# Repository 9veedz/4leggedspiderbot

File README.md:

# ESP32 Quadruped Spider Robot

> Built largely through vibe coding, iterating with an AI assistant rather than writing every line from scratch. Logic has been tested where possible, but review the code yourself before trusting it on real hardware, especially the servo angle limits.

A 4-legged (12-servo) walking robot controlled by an ESP32, with a built-in WiFi access point and web-based control interface for live tuning, calibration, and gait control — no app required, just a browser.

>  **This project is sponsored by [PCBWay](https://www.pcbway.com)!**

Many thanks to PCBWay for sponsoring this project with high-quality PCBs. As a small hobby project with no real following or funding, being approached by PCBWay for sponsorship genuinely means a lot. I'm truly grateful for the support — it's what made getting real boards in my hands possible. More details in the [sponsor section](#sponsor--pcbway) below.

> ⚠️ This is an ongoing hobby project — still actively being developed and subject to changes.
## Demo

**Walking gait**

**Body roll & pitch control**

> The robot moves significantly more fluidly than the videos suggest — the choppy appearance is purely down to the low frame rate of the recording. The inverse kinematics system interpolates each leg smoothly in real time; what you're seeing is a capture artifact, not the actual motion quality.

## Features

- **Inverse kinematics leg control** — each leg independently computes coxa/femur/tibia servo angles from X/Y/Z target positions.
- **Live web UI** — connects directly to the ESP32's own WiFi access point and serves a mobile-friendly control panel over WebSocket (`/ws`) with a captive portal so it opens automatically on connect.
- **Body posture control** — adjustable body height, width, stride length, pitch, and roll, with automatic tilt trim calculation per leg.
- **Walking gaits** — forward and reverse walking gaits using a diagonal-pair stepping pattern (lift → stride → push → recover).
- **Per-leg calibration** — manual servo angle control, configurable min/max safety limits, and offset trims per joint (coxa/femur/tibia), saved persistently to flash (ESP32 NVS/Preferences).
- **Per-leg power control** — individually or globally power legs on/off (releases servo PWM signal) for safe handling or storage.
- **Robot state machine** — `SIT`, `STAND`, `FORWARD`, `REVERSE` states drive automatic transitions between resting and walking behavior.

## Hardware

- ESP32 development board
- PCA9685 16-channel PWM/servo driver (I2C)
- 12x servos (3 per leg: coxa, femur, tibia)
- 4-leg chassis, with legs 1 and 2 mirrored relative to legs 0 and 3
- 3D-printed body: [Thingiverse Thing #2204279](https://www.thingiverse.com/thing:2204279), based on the design from [Instructables: DIY Spider Robot / Quad Robot / Quadruped](https://www.instructables.com/DIY-Spider-RobotQuad-robot-Quadruped/)

> **Important — before assembling the legs onto the 3D-printed body:** power each servo individually and set it to **90 degrees** *before* mounting the horn and locking the leg segments onto the printed body. The codebase has calls toward a `spiderCalibrate()` / `calibrateServos()` path, but it is not a complete, working calibration setup as-is — don't rely on it out of the box. Manually centering each servo to 90° before assembly (e.g. with a basic standalone test sketch) is the safer approach until calibration is properly wired up. The IK math and default offsets (`offC`/`offF`/`offT` = 90) assume each joint's mechanical zero/center point lines up with 90° on the servo. If a horn is attached and the leg geometry locked in at the wrong angle, the leg will be physically offset from where the code thinks it is, and you'll fight it with calibration offsets indefinitely instead of starting from a clean baseline.

| Leg | Coxa Pin | Femur Pin | Tibia Pin | Position    | Mirrored |
| --- | -------- | --------- | --------- | ----------- | -------- |
| 0   | 0        | 1         | 2         | Front-left  | No       |
| 1   | 3        | 4         | 5         | Front-right | Yes      |
| 2   | 6        | 7         | 8         | Back-left   | Yes      |
| 3   | 9        | 10        | 11        | Back-right  | No       |

### Leg Segment Lengths

Each leg has three segments, defined as constants in `SpiderLeg.cpp` and used directly in the inverse kinematics calculations:

| Segment | Joint | Length (mm) | Description                                |
| ------- | ----- | ----------- | ------------------------------------------ |
| L1      | Coxa  | 27.5        | Hip joint offset, rotates leg in X/Y plane |
| L2      | Femur | 55.0        | Upper leg segment                          |
| L3      | Tibia | 77.5        | Lower leg segment, reaches the ground      |

These are physical measurements of the chassis/leg hardware, used by `calculateIK()` to solve for coxa, femur, and tibia joint angles from a target X/Y/Z foot position. If you build this on different hardware, these three constants are the first thing to update to match your own leg dimensions.

## Project Structure

This is an Arduino IDE sketch. Arduino IDE requires a `.ino` file matching the sketch folder name, but all real logic lives in standard `.cpp`/`.h` files, which the IDE compiles automatically alongside it.

```
code/
├── SpiderRobot.ino     # Entry point: setup() / loop()
├── Spider.h / .cpp     # High-level robot behavior: stand, sit, walk, calibrate
├── SpiderLeg.h / .cpp  # Per-leg inverse kinematics & servo output
├── Robotstate.h / .cpp # Shared global state, persistence (flash/NVS)
├── Spiderserver.h / .cpp # WiFi AP, captive portal, WebSocket server
└── Webpage.h           # Embedded HTML/CSS/JS control panel (served from flash)
```

## Code Structure Notes

Each leg is its own object with its own pins and position, and handles its own mirroring internally. `Spider` just tells legs where to go. Makes gait code easier to read, and adding more legs later is mostly just adding more leg objects.

## Getting Started

1. Open `SpiderRobot.ino` in Arduino IDE.
2. Install required libraries via Library Manager:
  - `Adafruit PWM Servo Driver Library`
  - `ESPAsyncWebServer`
  - `AsyncTCP`
  - `ArduinoJson`
  - `DNSServer` (bundled with ESP32 core)
3. Select your ESP32 board under **Tools > Board**.
4. Wire the PCA9685 to the ESP32 via I2C and connect all 12 servos.
5. Flash the sketch.
6. On boot, the ESP32 creates a WiFi access point:
  - **SSID:** `ESP32_Spider`
  - **Password:** `12345678`
7. Connect to that network from a phone or laptop. A captive portal should prompt you to open the control page automatically (or browse to `192.168.4.1` manually).

> **Note:** The AP credentials are currently hardcoded in `Spiderserver.cpp`. Change them before deploying anywhere you don't fully control.

## Using the Web Interface

- **Robot Motion State** — switch between Sit / Stand / Forward / Reverse.
- **Body / Global** — tune body height, width, stride, pitch, and roll in real time.
- **Leg Select & Power** — choose which leg's parameters you're editing, and power individual or all legs on/off.
- **Geometry** — per-leg W/H/L trim offsets.
- **Servo Offsets** — per-joint calibration offsets (coxa/femur/tibia).
- **Servo Angle Control** — manually drive a joint to a specific angle (calibration mode).
- **Servo Min/Max** — set safe angle limits per joint to protect hardware.
- **Save to Flash** — persists all current settings to the ESP32's non-volatile storage.
- **Reload/Reset Defaults** — restores factory default values.

All changes apply live over WebSocket; no page reloads are needed.

## Understanding the Inverse Kinematics

If you want to understand how the leg IK math works before diving into `SpiderLeg.cpp`, this video explains it well:

📺 [Inverse Kinematics for a 3-segment leg — YouTube](https://youtu.be/HjmIOKSp7v4?si=qGuz0ecaw_1wg7XF)

## How to Swap in Your Own Control Scheme

The main robot logic lives in `SpiderLeg`, `Spider`, and `Robotstate` — those are the brains. `Spiderserver` and `Webpage` are just how *this* project talks to the robot over WiFi/WebSocket. You can rip those out entirely and replace them with whatever you want — a Bluetooth remote, an RC receiver, a gamepad, a serial interface — as long as you write to the same variables in `Robotstate`.

Everything the robot responds to is exposed as simple global variables you can read or write from anywhere:

**Body / Posture**

| Variable     | Type    | Description                       |
| ------------ | ------- | --------------------------------- |
| `bodyHeight` | `float` | Overall body height offset        |
| `bodyWidth`  | `float` | Overall body width offset         |
| `bodyStride` | `float` | Step length used in walking gaits |
| `bodyPitch`  | `float` | Forward/back tilt of the body     |
| `bodyRoll`   | `float` | Left/right tilt of the body       |

**Robot State**

| Variable         | Type             | Description                                                                                                                                            |
| ---------------- | ---------------- | ------------------------------------------------------------------------------------------------------------------------------------------------------ |
| `commandedState` | `RobotStateMode` | What you want the robot to do: `SIT`, `STAND`, `FORWARD`, `REVERSE`                                                                                    |
| `currentState`   | `RobotStateMode` | What the robot is currently doing — declared but not yet actively updated separately from `commandedState`, reserved for future state transition logic |
| `activeLeg`      | `int`            | Which leg (0–3) is selected for tuning                                                                                                                 |
| `calibrateMode`  | `bool`           | ⚠️ Declared but currently unused — reserved for a future calibration mode flow                                                                         |
| `calibrateLeg`   | `int`            | ⚠️ Declared but currently unused — intended to track which leg is being calibrated independently of `activeLeg`                                        |

**Computed Per-Leg Arrays** (auto-updated by `updateKinematicArrays()`)

| Variable        | Type    | Description                                         |
| --------------- | ------- | --------------------------------------------------- |
| `legHeights[4]` | `float` | Effective height per leg after pitch/roll tilt trim |
| `legWidths[4]`  | `float` | Effective width per leg                             |

**Per-Leg Parameters** (`legs[0]` through `legs[3]`)

| Field                      | Type    | Description                                                                                                            |
| -------------------------- | ------- | ---------------------------------------------------------------------------------------------------------------------- |
| `W`                        | `float` | Manual width trim for this leg                                                                                         |
| `H`                        | `float` | Manual height trim for this leg                                                                                        |
| `L`                        | `float` | Lift height used during gait steps                                                                                     |
| `offC / offF / offT`       | `float` | Calibration angle offset per joint (coxa/femur/tibia)                                                                  |
| `servoC / servoF / servoT` | `int`   | Raw manual servo angle (used in calibration mode)                                                                      |
| `cMin/cMax`                | `int`   | Coxa joint safe angle limits                                                                                           |
| `fMin/fMax`                | `int`   | Femur joint safe angle limits                                                                                          |
| `tMin/tMax`                | `int`   | Tibia joint safe angle limits                                                                                          |
| `X / Y / Z`                | `float` | ⚠️ Stored and persisted but not yet actively read back into gait logic — reserved for future per-leg position tracking |
| `powerDisabled`            | `bool`  | If true, this leg's servos are powered off                                                                             |

- `Robotstate` holds all shared configuration (body posture, per-leg parameters, current/commanded state) and computes derived kinematic arrays (`legHeights`, `legWidths`) whenever body posture changes, including tilt trim from pitch/roll.
- `SpiderLeg` converts target X/Y/Z leg positions into joint angles via geometric inverse kinematics, then maps those angles to PWM pulses, accounting for whether the leg is mirrored.
- `Spider` orchestrates all four legs together — gait sequencing for walking, synchronized sit/stand/center routines, and calibration mode.
- `Spiderserver` hosts the WiFi AP, captive portal DNS, and WebSocket server, parsing simple text commands (e.g. `bodyHeight=70.0`, `leg=2 offC=85`) from the web UI and broadcasting updated state back to all connected clients.

## PCB

The wiring was getting pretty messy and the space inside the 3D-printed body is quite constrained so the natural next step was to design a proper PCB to clean everything up. Luckily, [PCBWay](https://www.pcbway.com) reached out about a collaboration and sponsored the boards for this project. As a small hobby build with no real following or funding, that was honestly unexpected and really appreciated.

The PCB went through 2 design revisions with a total of 3 boards including a stacked voltage divider board for reading servo positions(under development). Full details, schematics, and board photos are in the PCB folder:

## Sponsor — PCBWay

I'm really grateful to **[PCBWay](https://www.pcbway.com)** for sponsoring the PCBs for this project. 
As a hobby engineer doing this on my own time and budget, getting sponsored boards was a massive help and I honestly wasn't expecting the quality to be this good.

### What is PCBWay?

PCBWay is a PCB manufacturer and fab service out of Shenzhen. They do pretty much everything:

- PCB fabrication (single layer all the way up to 20+ layers, rigid, flex, rigid-flex)
- PCB assembly (SMT + through-hole, full turnkey)
- 3D printing (FDM, SLA, SLS, and even metal)
- CNC machining and sheet metal
- One-stop prototyping for small runs

Their online quote tool is instant and the turnaround is genuinely fast standard boards can ship in 24 hours.

---

My Experience

The spiderbot boards aren't super complex but they're not trivial either 12 servo channels, multiple power rails, a stackup between two boards. I uploaded my Gerbers and got a quote almost immediately, no back and forth.

**Ordering was straightforward:**
1. Exported Gerbers and drill files from KiCad and compressed them into a single zip file
2. Uploaded to the PCBWay portal
3. Most of the parameters are selected by default from the gerber files but you can customize according to your requirements
4. Order confirmed and out the door within 24 hours

**When the boards arrived:**
- Well packed anti-static bags inside a solid mailer, no damage
- V-score lines on the panel were clean and snapped apart easily
- Soldermask was crisp, silkscreen was readable, no bridging on any pads

**Received Boards**

**Dimensions held up:**
- Outline matched my design within ±0.1mm
- Vias and traces exactly as in the Gerbers
- Stacking fit between the two boards was spot on

Honestly for a hobby project like this, PCBWay hit the sweet spot of quality, speed, and price. If you're building something similar definitely worth checking them out → [pcbway.com](https://www.pcbway.com)

→ [PCB README — designs, components, and build notes](PCB/readme(2).md)

## Future Notes

Planned / possible extensions, made straightforward by the existing modular structure:

- **More walking patterns** — turning (left/right), crab walk (lateral movement using the existing `crab()` primitive in `SpiderLeg`), and a dance routine are planned. The gait system is structured as a phase/substep state machine in `Spider.cpp`, so new patterns slot in as additional `walkX()` methods without touching the leg kinematics.
- **IMU-based balancing** — add an IMU (e.g. MPU6050) and feed pitch/roll readings into a PID loop that continuously adjusts `bodyPitch`/`bodyRoll` (or per-leg height directly) to keep the body level on uneven terrain. Since `updateKinematicArrays()` already recalculates per-leg height/width trim from `bodyPitch`/`bodyRoll` via `calculateTiltTrim()`, this mostly means replacing manual slider input with a PID controller's output on the same variables — no kinematics rewrite needed.
- **Remote control input** — because all robot control already flows through simple state changes (`commandedState`, `bodyHeight`, `bodyWidth`, etc. in `Robotstate`) rather than being tightly coupled to the WebSocket parser, an RC receiver, Bluetooth gamepad, or other remote input method can be added as just another input source writing to those same variables, alongside or instead of the web UI.

The decoupled design (state in `Robotstate`, kinematics in `SpiderLeg`, orchestration in `Spider`, I/O in `Spiderserver`) means new input/sensor sources generally plug into the *existing* state variables rather than requiring changes to gait logic or IK code.

## License

CC BY-NC-SA 4.0 (Attribution-NonCommercial-ShareAlike) — see [LICENSE](LICENSE) for details. Free for personal/non-commercial use and modification with credit to `9veedz`; selling this project or derivatives of it is not permitted.

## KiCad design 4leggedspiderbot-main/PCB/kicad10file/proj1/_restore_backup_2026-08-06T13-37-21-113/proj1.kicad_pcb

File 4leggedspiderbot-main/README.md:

# ESP32 Quadruped Spider Robot

> Built largely through vibe coding — iterating with an AI assistant rather than writing every line from scratch. Logic has been tested where possible, but review the code yourself before trusting it on real hardware, especially the servo angle limits.

A 4-legged (12-servo) walking robot controlled by an ESP32, with a built-in WiFi access point and web-based control interface for live tuning, calibration, and gait control — no app required, just a browser.

## Demo

**Walking gait**

**Body roll & pitch control**

> The robot moves significantly more fluidly than the videos suggest — the choppy appearance is purely down to the low frame rate of the recording. The inverse kinematics system interpolates each leg smoothly in real time; what you're seeing is a capture artifact, not the actual motion quality.

## Features

- **Inverse kinematics leg control** — each leg independently computes coxa/femur/tibia servo angles from X/Y/Z target positions.
- **Live web UI** — connects directly to the ESP32's own WiFi access point and serves a mobile-friendly control panel over WebSocket (`/ws`) with a captive portal so it opens automatically on connect.
- **Body posture control** — adjustable body height, width, stride length, pitch, and roll, with automatic tilt trim calculation per leg.
- **Walking gaits** — forward and reverse walking gaits using a diagonal-pair stepping pattern (lift → stride → push → recover).
- **Per-leg calibration** — manual servo angle control, configurable min/max safety limits, and offset trims per joint (coxa/femur/tibia), saved persistently to flash (ESP32 NVS/Preferences).
- **Per-leg power control** — individually or globally power legs on/off (releases servo PWM signal) for safe handling or storage.
- **Robot state machine** — `SIT`, `STAND`, `FORWARD`, `REVERSE` states drive automatic transitions between resting and walking behavior.

## Hardware

- ESP32 development board
- PCA9685 16-channel PWM/servo driver (I2C)
- 12x servos (3 per leg: coxa, femur, tibia)
- 4-leg chassis, with legs 1 and 2 mirrored relative to legs 0 and 3
- 3D-printed body: [Thingiverse Thing #2204279](https://www.thingiverse.com/thing:2204279), based on the design from [Instructables: DIY Spider Robot / Quad Robot / Quadruped](https://www.instructables.com/DIY-Spider-RobotQuad-robot-Quadruped/)

> **Important — before assembling the legs onto the 3D-printed body:** power each servo individually and set it to **90 degrees** *before* mounting the horn and locking the leg segments onto the printed body. The codebase has calls toward a `spiderCalibrate()` / `calibrateServos()` path, but it is not a complete, working calibration setup as-is — don't rely on it out of the box. Manually centering each servo to 90° before assembly (e.g. with a basic standalone test sketch) is the safer approach until calibration is properly wired up. The IK math and default offsets (`offC`/`offF`/`offT` = 90) assume each joint's mechanical zero/center point lines up with 90° on the servo. If a horn is attached and the leg geometry locked in at the wrong angle, the leg will be physically offset from where the code thinks it is, and you'll fight it with calibration offsets indefinitely instead of starting from a clean baseline.

| Leg | Coxa Pin | Femur Pin | Tibia Pin | Position          | Mirrored |
|-----|----------|-----------|-----------|--------------------|----------|
| 0   | 0        | 1         | 2         | Front-left         | No       |
| 1   | 3        | 4         | 5         | Front-right        | Yes      |
| 2   | 6        | 7         | 8         | Back-left          | Yes      |
| 3   | 9        | 10        | 11        | Back-right         | No       |

### Leg Segment Lengths

Each leg has three segments, defined as constants in `SpiderLeg.cpp` and used directly in the inverse kinematics calculations:

| Segment | Joint  | Length (mm) | Description                                |
|---------|--------|-------------|---------------------------------------------|
| L1      | Coxa   | 27.5        | Hip joint offset, rotates leg in X/Y plane  |
| L2      | Femur  | 55.0        | Upper leg segment                           |
| L3      | Tibia  | 77.5        | Lower leg segment, reaches the ground       |

These are physical measurements of the chassis/leg hardware, used by `calculateIK()` to solve for coxa, femur, and tibia joint angles from a target X/Y/Z foot position. If you build this on different hardware, these three constants are the first thing to update to match your own leg dimensions.

## Project Structure

This is an Arduino IDE sketch. Arduino IDE requires a `.ino` file matching the sketch folder name, but all real logic lives in standard `.cpp`/`.h` files, which the IDE compiles automatically alongside it.

```
SpiderRobot/
├── SpiderRobot.ino     # Entry point: setup() / loop()
├── Spider.h / .cpp     # High-level robot behavior: stand, sit, walk, calibrate
├── SpiderLeg.h / .cpp  # Per-leg inverse kinematics & servo output
├── Robotstate.h / .cpp # Shared global state, persistence (flash/NVS)
├── Spiderserver.h / .cpp # WiFi AP, captive portal, WebSocket server
└── Webpage.h           # Embedded HTML/CSS/JS control panel (served from flash)
```

## Code Structure Notes

Each leg is its own object with its own pins and position, and handles its own mirroring internally. `Spider` just tells legs where to go. Makes gait code easier to read, and adding more legs later is mostly just adding more leg objects.

## Getting Started

1. Open `SpiderRobot.ino` in Arduino IDE.
2. Install required libraries via Library Manager:
   - `Adafruit PWM Servo Driver Library`
   - `ESPAsyncWebServer`
   - `AsyncTCP`
   - `ArduinoJson`
   - `DNSServer` (bundled with ESP32 core)
3. Select your ESP32 board under **Tools > Board**.
4. Wire the PCA9685 to the ESP32 via I2C and connect all 12 servos.
5. Flash the sketch.
6. On boot, the ESP32 creates a WiFi access point:
   - **SSID:** `ESP32_Spider`
   - **Password:** `12345678`
7. Connect to that network from a phone or laptop. A captive portal should prompt you to open the control page automatically (or browse to `192.168.4.1` manually).

> **Note:** The AP credentials are currently hardcoded in `Spiderserver.cpp`. Change them before deploying anywhere you don't fully control.

## Using the Web Interface

- **Robot Motion State** — switch between Sit / Stand / Forward / Reverse.
- **Body / Global** — tune body height, width, stride, pitch, and roll in real time.
- **Leg Select & Power** — choose which leg's parameters you're editing, and power individual or all legs on/off.
- **Geometry** — per-leg W/H/L trim offsets.
- **Servo Offsets** — per-joint calibration offsets (coxa/femur/tibia).
- **Servo Angle Control** — manually drive a joint to a specific angle (calibration mode).
- **Servo Min/Max** — set safe angle limits per joint to protect hardware.
- **Save to Flash** — persists all current settings to the ESP32's non-volatile storage.
- **Reload/Reset Defaults** — restores factory default values.

All changes apply live over WebSocket; no page reloads are needed.

## Understanding the Inverse Kinematics

If you want to understand how the leg IK math works before diving into `SpiderLeg.cpp`, this video explains it well:

📺 [Inverse Kinematics for a 3-segment leg — YouTube](https://youtu.be/HjmIOKSp7v4?si=qGuz0ecaw_1wg7XF)

## How to Swap in Your Own Control Scheme

The main robot logic lives in `SpiderLeg`, `Spider`, and `Robotstate` — those are the brains. `Spiderserver` and `Webpage` are just how *this* project talks to the robot over WiFi/WebSocket. You can rip those out entirely and replace them with whatever you want — a Bluetooth remote, an RC receiver, a gamepad, a serial interface — as long as you write to the same variables in `Robotstate`.

Everything the robot responds to is exposed as simple global variables you can read or write from anywhere:

**Body / Posture**
| Variable | Type | Description |
|---|---|---|
| `bodyHeight` | `float` | Overall body height offset |
| `bodyWidth` | `float` | Overall body width offset |
| `bodyStride` | `float` | Step length used in walking gaits |
| `bodyPitch` | `float` | Forward/back tilt of the body |
| `bodyRoll` | `float` | Left/right tilt of the body |

**Robot State**
| Variable | Type | Description |
|---|---|---|
| `commandedState` | `RobotStateMode` | What you want the robot to do: `SIT`, `STAND`, `FORWARD`, `REVERSE` |
| `currentState` | `RobotStateMode` | What the robot is currently doing — declared but not yet actively updated separately from `commandedState`, reserved for future state transition logic |
| `activeLeg` | `int` | Which leg (0–3) is selected for tuning |
| `calibrateMode` | `bool` | ⚠️ Declared but currently unused — reserved for a future calibration mode flow |
| `calibrateLeg` | `int` | ⚠️ Declared but currently unused — intended to track which leg is being calibrated independently of `activeLeg` |

**Computed Per-Leg Arrays** (auto-updated by `updateKinematicArrays()`)
| Variable | Type | Description |
|---|---|---|
| `legHeights[4]` | `float` | Effective height per leg after pitch/roll tilt trim |
| `legWidths[4]` | `float` | Effective width per leg |

**Per-Leg Parameters** (`legs[0]` through `legs[3]`)
| Field | Type | Description |
|---|---|---|
| `W` | `float` | Manual width trim for this leg |
| `H` | `float` | Manual height trim for this leg |
| `L` | `float` | Lift height used during gait steps |
| `offC / offF / offT` | `float` | Calibration angle offset per joint (coxa/femur/tibia) |
| `servoC / servoF / servoT` | `int` | Raw manual servo angle (used in calibration mode) |
| `cMin/cMax` | `int` | Coxa joint safe angle limits |
| `fMin/fMax` | `int` | Femur joint safe angle limits |
| `tMin/tMax` | `int` | Tibia joint safe angle limits |
| `X / Y / Z` | `float` | ⚠️ Stored and persisted but not yet actively read back into gait logic — reserved for future per-leg position tracking |
| `powerDisabled` | `bool` | If true, this leg's servos are powered off |

- `Robotstate` holds all shared configuration (body posture, per-leg parameters, current/commanded state) and computes derived kinematic arrays (`legHeights`, `legWidths`) whenever body posture changes, including tilt trim from pitch/roll.
- `SpiderLeg` converts target X/Y/Z leg positions into joint angles via geometric inverse kinematics, then maps those angles to PWM pulses, accounting for whether the leg is mirrored.
- `Spider` orchestrates all four legs together — gait sequencing for walking, synchronized sit/stand/center routines, and calibration mode.
- `Spiderserver` hosts the WiFi AP, captive portal DNS, and WebSocket server, parsing simple text commands (e.g. `bodyHeight=70.0`, `leg=2 offC=85`) from the web UI and broadcasting updated state back to all connected clients.

## Future Notes

Planned / possible extensions, made straightforward by the existing modular structure:

- **More walking patterns** — turning (left/right), crab walk (lateral movement using the existing `crab()` primitive in `SpiderLeg`), and a dance routine are planned. The gait system is structured as a phase/substep state machine in `Spider.cpp`, so new patterns slot in as additional `walkX()` methods without touching the leg kinematics.
- **IMU-based balancing** — add an IMU (e.g. MPU6050) and feed pitch/roll readings into a PID loop that continuously adjusts `bodyPitch`/`bodyRoll` (or per-leg height directly) to keep the body level on uneven terrain. Since `updateKinematicArrays()` already recalculates per-leg height/width trim from `bodyPitch`/`bodyRoll` via `calculateTiltTrim()`, this mostly means replacing manual slider input with a PID controller's output on the same variables — no kinematics rewrite needed.
- **Remote control input** — because all robot control already flows through simple state changes (`commandedState`, `bodyHeight`, `bodyWidth`, etc. in `Robotstate`) rather than being tightly coupled to the WebSocket parser, an RC receiver, Bluetooth gamepad, or other remote input method can be added as just another input source writing to those same variables, alongside or instead of the web UI.

The decoupled design (state in `Robotstate`, kinematics in `SpiderLeg`, orchestration in `Spider`, I/O in `Spiderserver`) means new input/sensor sources generally plug into the *existing* state variables rather than requiring changes to gait logic or IK code.

## License

CC BY-NC-SA 4.0 (Attribution-NonCommercial-ShareAlike) — see [LICENSE](./LICENSE) for details. Free for personal/non-commercial use and modification with credit to `9veedz`; selling this project or derivatives of it is not permitted.

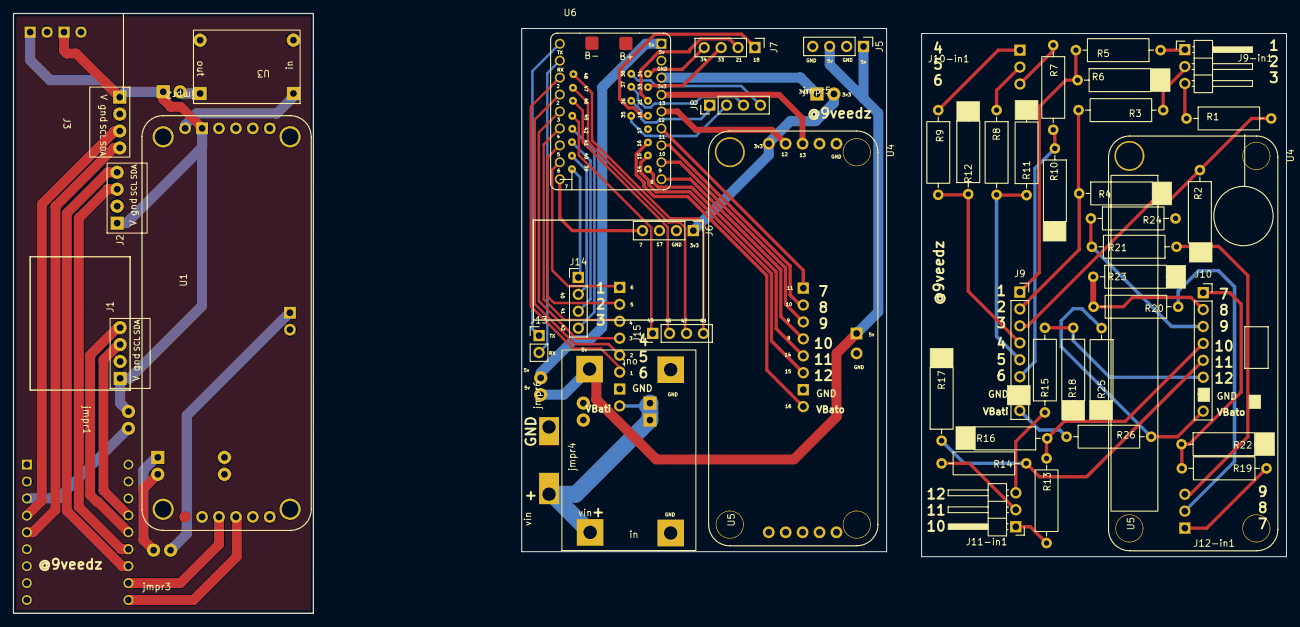
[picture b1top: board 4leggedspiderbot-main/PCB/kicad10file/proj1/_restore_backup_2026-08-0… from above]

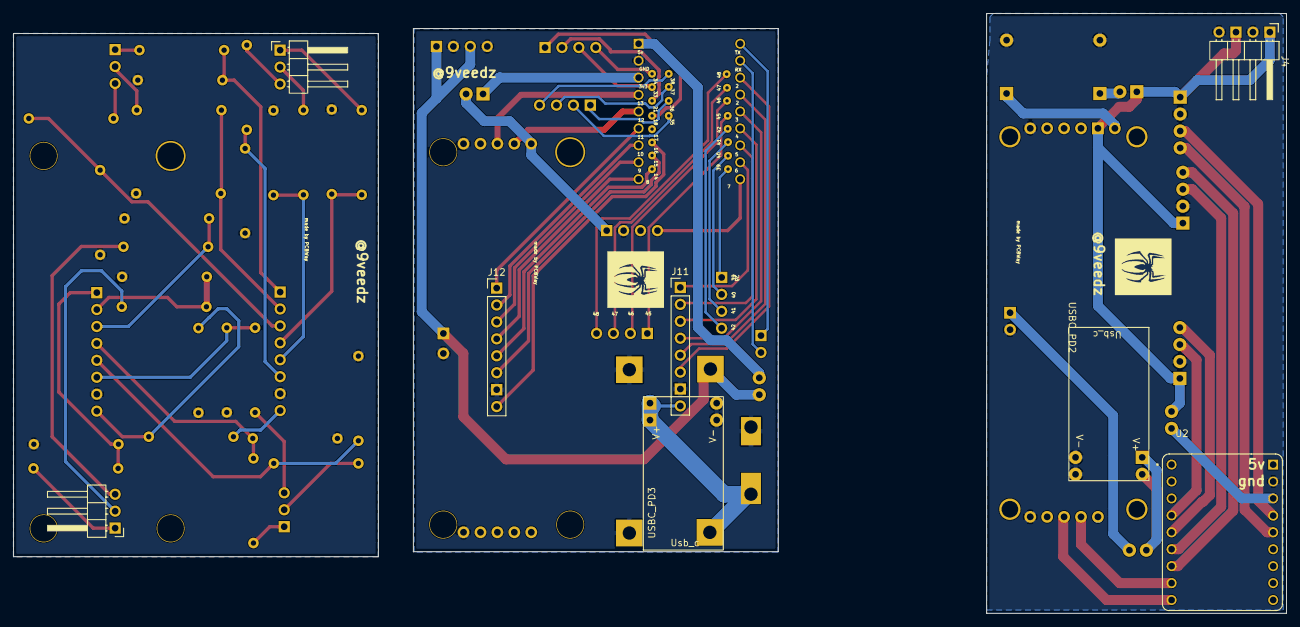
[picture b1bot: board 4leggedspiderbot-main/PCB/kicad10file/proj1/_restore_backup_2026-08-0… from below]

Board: 2 copper layers, 191.0 x 90.0 mm, 60 parts (8 on the bottom side), 80 nets.

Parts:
J1, J2, J3: Conn_01x04; 4con
J4: Conn_01x04; PinHeader_1x04_P2.54mm_Horizontal
J5, J6, J7, J8, J14, J15: Conn_01x04; PinHeader_1x04_P2.54mm_Vertical
J9, J10: Conn_01x08; PinSocket_1x08_P2.54mm_Vertical
J9-in1, J10-in1, J11-in1, J12-in1: Conn_01x03; PinHeader_1x03_P2.54mm_Horizontal
J11, J12: Conn_01x08; PinHeader_1x08_P2.54mm_Vertical
J13: Conn_01x02; PinHeader_1x02_P2.54mm_Vertical
R1, R3, R5, R7, R8, R9, R13, R14, R15, R19, R20, R21, R25: 10k; R_Axial_DIN0309_L9.0mm_D3.2mm_P12.70mm_Horizontal
R2, R4, R6, R10, R11, R12, R16, R17, R18, R22, R23, R24: 20k; R_Axial_DIN0309_L9.0mm_D3.2mm_P12.70mm_Horizontal
R26: 18k; R_Axial_DIN0309_L9.0mm_D3.2mm_P12.70mm_Horizontal
U1, U4, U4#2: 815; MODULE_815
U2, U6: ESP32-S3; ESP32-S3-SuperMini
U3, U5: dc-3.3
USBC_PD2, USBC_PD3: Untitled_1
jmpr1, jmpr2, jmpr3, jmpr4, jmpr5, jmpr6: jmpr

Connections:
GND: J1.2, J2.2, J3.2, J4.2, J4.4, J5.2, J5.4, J6.2, J9.7, J10.7, J11.7, J12.7, R2.2, R4.2, R6.2, R10.2, R11.2, R12.2, R16.2, R17.2, R18.2, R22.2, R23.2, R24.2, R25.2, U1.GND_1 (GND), U1.GND_2 (GND), U1.GND_18 (GND), U2.GND, U3.2 (gnd), U3.4 (gnd), U4#2.GND_1 (GND), U4#2.GND_2 (GND), U5.2 (gnd), U5.4 (gnd), U6.GND, USBC_PD2.3 (gnd), USBC_PD2.4 (gnd), USBC_PD3.3 (gnd), USBC_PD3.4 (gnd), jmpr4.2
unnamed: J1.3, U2.2 (GPIO2/ADC1_CH1)
unnamed: J1.4, U2.3 (GPIO3/ADC1_CH2)
unnamed: J2.3, U2.4 (GPIO4/ADC1_CH3)
unnamed: J2.4, U2.5 (GPIO5/ADC1_CH4)
unnamed: J3.3, U2.13 (GPIO13/ADC2_CH2)
unnamed: J3.4, U2.12 (GPIO12/ADC2_CH1)
unnamed: J6.3, U6.17 (GPIO17/ADC2_CH6)
unnamed: J6.4, U6.7 (GPIO7/ADC1_CH6)
unnamed: J7.1, U6.18 (GPIO18/ADC2_CH7)
unnamed: J7.2, U6.21 (GPIO21)
unnamed: J7.3, U6.33 (GPIO33)
unnamed: J7.4, U6.34 (GPIO34)
unnamed: J8.1, U6.36 (GPIO36)
unnamed: J8.2, U6.35 (GPIO35)
unnamed: J8.3, U6.37 (GPIO37)
unnamed: J8.4, U6.38 (GPIO38)
unnamed: J9.1, R5.2, R6.1
unnamed: J9.2, R3.2, R4.1
unnamed: J9.3, R1.2, R2.1
unnamed: J9.4, R9.2, R12.1
unnamed: J9.5, R8.2, R11.1
unnamed: J9.6, R7.2, R10.1
unnamed: J9.8, R26.1
unnamed: J9-in1.1, R5.1
unnamed: J9-in1.2, R3.1
unnamed: J9-in1.3, R1.1
unnamed: J10.1, R19.2, R22.1
unnamed: J10.2, R20.2, R23.1
unnamed: J10.3, R21.2, R24.1
unnamed: J10.4, R13.2, R16.1
unnamed: J10.5, R14.2, R17.1
unnamed: J10.6, R15.2, R18.1
unnamed: J10.8, R25.1, R26.2
unnamed: J10-in1.1, R9.1
unnamed: J10-in1.2, R8.1
unnamed: J10-in1.3, R7.1
unnamed: J11.1, U6.6 (GPIO6/ADC1_CH5)
unnamed: J11.2, U6.5 (GPIO5/ADC1_CH4)
unnamed: J11.3, U6.4 (GPIO4/ADC1_CH3)
unnamed: J11.4, U6.3 (GPIO3/ADC1_CH2)
unnamed: J11.5, U6.2 (GPIO2/ADC1_CH1)
unnamed: J11.6, U6.1 (GPIO1/ADC1_CH0)
unnamed: J11.8, USBC_PD3.1 (v+), jmpr4.1
unnamed: J11-in1.1, R13.1
unnamed: J11-in1.2, R14.1
unnamed: J11-in1.3, R15.1
unnamed: J12.1, U6.11 (GPIO11/ADC2_CH0)
unnamed: J12.2, U6.10 (GPIO10/ADC1_CH9)
unnamed: J12.3, U6.9 (GPIO9/ADC1_CH8)
unnamed: J12.4, U6.8 (GPIO8/ADC1_CH7)
unnamed: J12.5, U6.14 (GPIO14/ADC2_CH3)
unnamed: J12.6, U6.15 (GPIO15/ADC2_CH4/XTAL_32K_P)
unnamed: J12.8, U6.16 (GPIO16/ADC2_CH5/XTAL_32K_N)
unnamed: J12-in1.1, R19.1
unnamed: J12-in1.2, R20.1
unnamed: J12-in1.3, R21.1
unnamed: J13.1, U6.TX (U0TXD/PROG/GPIO43)
unnamed: J13.2, U6.RX (U0RXD/PROG/GPIO44)
unnamed: J14.1, U6.39 (MTCK/JTAG/GPIO39)
unnamed: J14.2, U6.40 (MTDO/JTAG/GPIO40)
unnamed: J14.3, U6.41 (MTDI/JTAG/GPIO41)
unnamed: J14.4, U6.42 (MTMS/JTAG/GPIO42)
unnamed: J15.1, U6.45 (GPIO45)
unnamed: J15.2, U6.46 (GPIO46)
unnamed: J15.3, U6.47 (SPICLK_P/GPIO47)
unnamed: J15.4, U6.48 (SPICLK_N/GPIO48)
unnamed: U1.OE_1 (~OE), U1.OE_2 (~OE)
unnamed: U1.SDA_1 (SDA), U1.SDA_2 (SDA), U2.6 (GPIO6/ADC1_CH5)
unnamed: U1.SCL_1 (SCL), U1.SCL_2 (SCL), U2.7 (GPIO7/ADC1_CH6)
unnamed: U3.3 (out+), jmpr2.1
unnamed: U4#2.OE_1 (~OE), U4#2.OE_2 (~OE)
unnamed: U5.1 (In+), USBC_PD3.2 (v+)
unnamed: U4#2.SDA_1 (SDA), U4#2.SDA_2 (SDA), U6.12 (GPIO12/ADC2_CH1)
unnamed: U4#2.SCL_1 (SCL), U4#2.SCL_2 (SCL), U6.13 (GPIO13/ADC2_CH2)
unnamed: U6.5v (VDDA), jmpr6.2
unnamed: USBC_PD2.1 (v+), USBC_PD2.2 (v+), jmpr3.1
V+: J5.1, J5.3, U1.V+_1 (V+), U1.V+_2 (V+), U1.V+_18 (V+), U3.1 (In+), U5.3 (out+), jmpr3.2, jmpr6.1
VCC: J1.1, J2.1, J3.1, J4.1, J4.3, J6.1, U1.VCC_1 (VCC), U1.VCC_2 (VCC), U4#2.VCC_1 (VCC), U4#2.VCC_2 (VCC), jmpr1.1, jmpr2.2, jmpr5.2
VDD3P3: U2.3V3 (VDD3P3), U6.3V3 (VDD3P3), jmpr1.2, jmpr5.1

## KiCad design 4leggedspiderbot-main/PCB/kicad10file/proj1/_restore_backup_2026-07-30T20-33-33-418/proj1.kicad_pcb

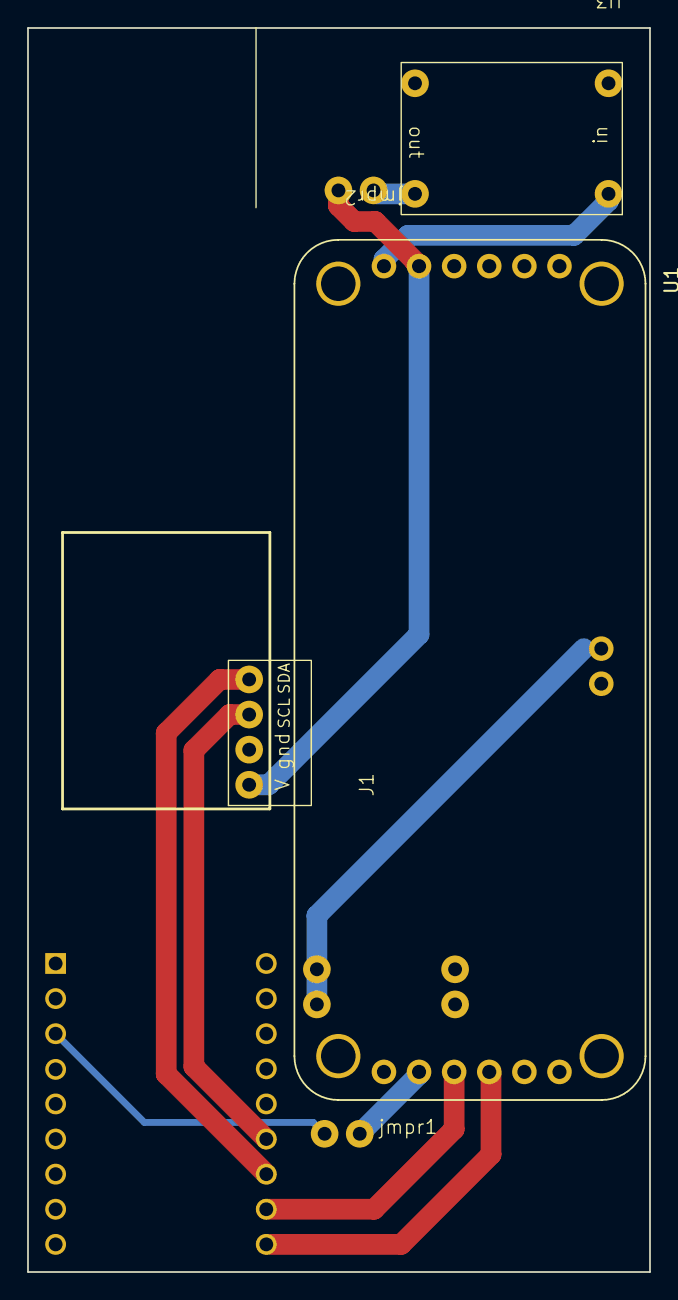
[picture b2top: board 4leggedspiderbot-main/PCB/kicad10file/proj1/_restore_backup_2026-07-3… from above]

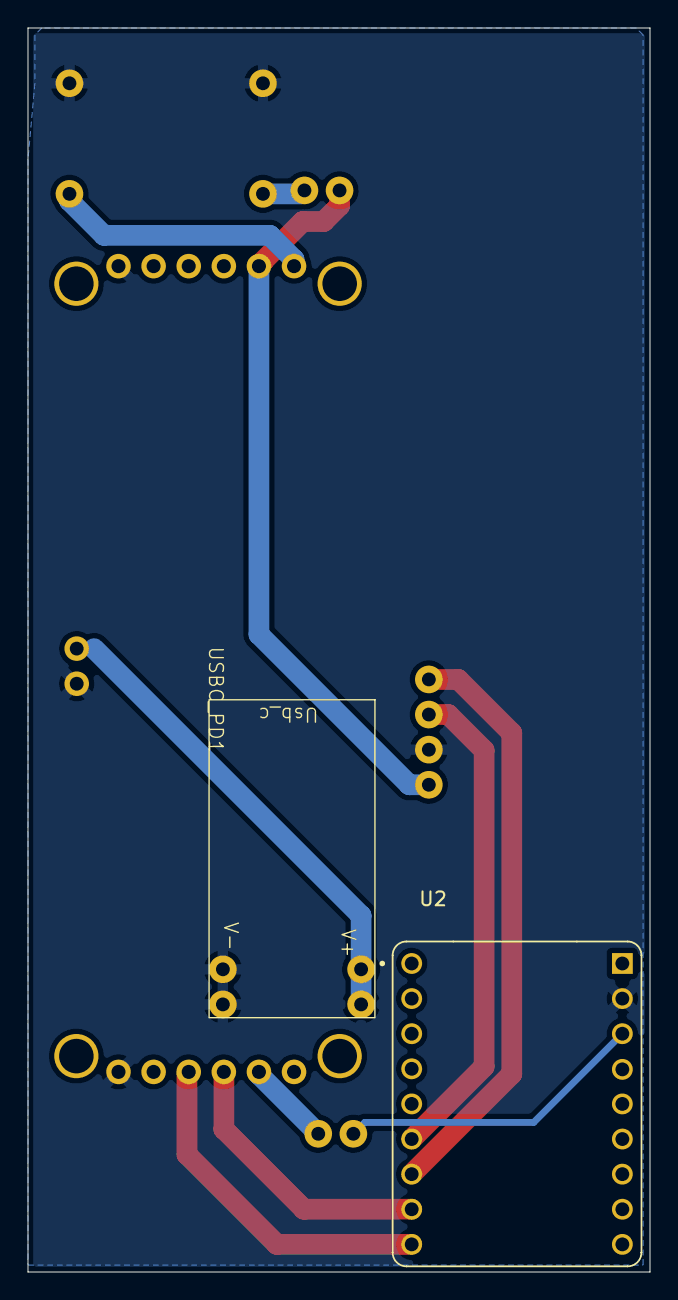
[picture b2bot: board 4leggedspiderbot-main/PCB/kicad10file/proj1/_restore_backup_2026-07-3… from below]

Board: 2 copper layers, 45.0 x 90.0 mm, 7 parts (2 on the bottom side), 8 nets.

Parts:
J1: Conn_01x04; 4con
U1: 815; MODULE_815
U2: ESP32-S3; ESP32-S3-SuperMini
U3: dc-3.3
USBC_PD1: Untitled_1
jmpr1, jmpr2: jmpr

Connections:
GND: J1.2, U1.GND_1 (GND), U1.GND_2 (GND), U1.GND_18 (GND), U2.GND, U3.2 (gnd), U3.4 (gnd), USBC_PD1.2 (V-), USBC_PD1.3, USBC_PD1.4
unnamed: J1.3, U2.4 (CHIP_PU/RESET)
unnamed: J1.4, U2.5 (GPIO0/BOOT)
unnamed: U1.SDA_1 (SDA), U1.SDA_2 (SDA), U2.6 (GPIO1/ADC1_CH0)
unnamed: U1.OE_1 (~OE), U1.OE_2 (~OE), U1.SCL_1 (SCL), U1.SCL_2 (SCL), U2.7 (GPIO2/ADC1_CH1)
V+: U1.V+_1 (V+), U1.V+_2 (V+), U1.V+_18 (V+), U3.1 (In+), USBC_PD1.1 (V+)
VCC: J1.1, U1.VCC_1 (VCC), U1.VCC_2 (VCC)
VDD3P3: U2.2 (VDD3P3), U2.3 (VDD3P3)
